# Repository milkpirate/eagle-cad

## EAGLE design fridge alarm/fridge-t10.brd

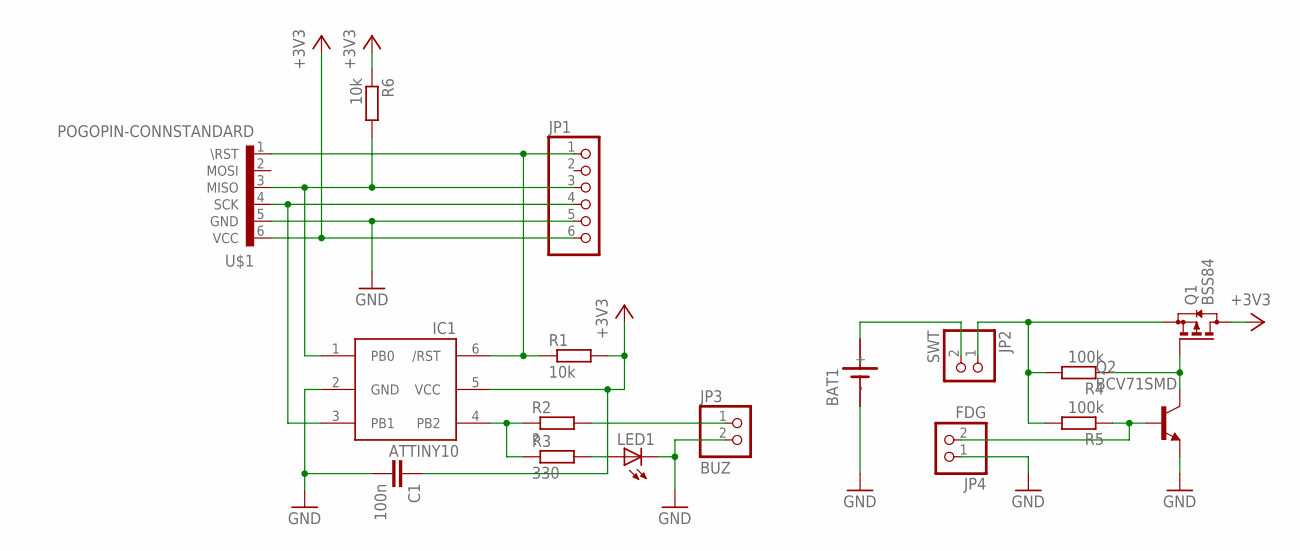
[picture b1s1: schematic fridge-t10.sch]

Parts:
BAT1: SN2032
C1: 100n; C0805K
IC1: ATTINY10; SOT23-6
JP1: PINHD-1X6; 1X06
JP2: SWT; 1X02
JP3: BUZ; 1X02
JP4: FDG; 1X02
LED1: LEDCHIPLED_0805; CHIPLED_0805
Q1: BSS84; SOT23
Q2: BCV71SMD; SOT23-BEC
R1, R6: 10k; R0805
R2: ?; R0805
R3: 330; R0805
R4, R5: 100k; R0805
U$1: POGOPIN-CONNSTANDARD; POGOPROG-CONN

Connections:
+3V3: C1.1, IC1.5 (VCC), JP1.6, Q1.3 (D), R1.2, R6.1, U$1.6 (VCC)
GND: BAT1.-, C1.2, IC1.2 (GND), JP1.5, JP3.2, JP4.1, LED1.C, Q2.E, U$1.5 (GND)
unnamed: BAT1.+, JP2.2
unnamed: IC1.4 (PB2), R2.1, R3.1
unnamed: IC1.1 (PB0), JP1.3, R6.2, U$1.3 (MISO)
unnamed: LED1.A, R3.2
unnamed: IC1.6 (/RST), JP1.1, R1.1, U$1.1 (\RST)
unnamed: JP3.1, R2.2
unnamed: JP2.1, Q1.2 (S), R4.2, R5.2
unnamed: IC1.3 (PB1), JP1.4, U$1.4 (SCK)
unnamed: JP4.2, Q2.B, R5.1
unnamed: Q1.1 (G), Q2.C, R4.1

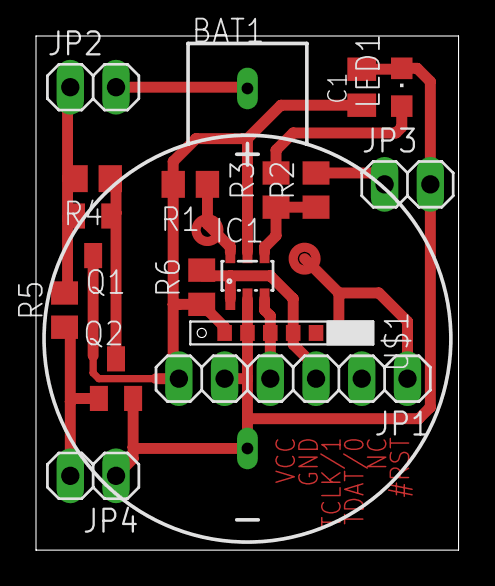
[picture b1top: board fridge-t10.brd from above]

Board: 2 copper layers, 23.5 x 28.6 mm, 17 parts (0 on the bottom side), 12 nets.

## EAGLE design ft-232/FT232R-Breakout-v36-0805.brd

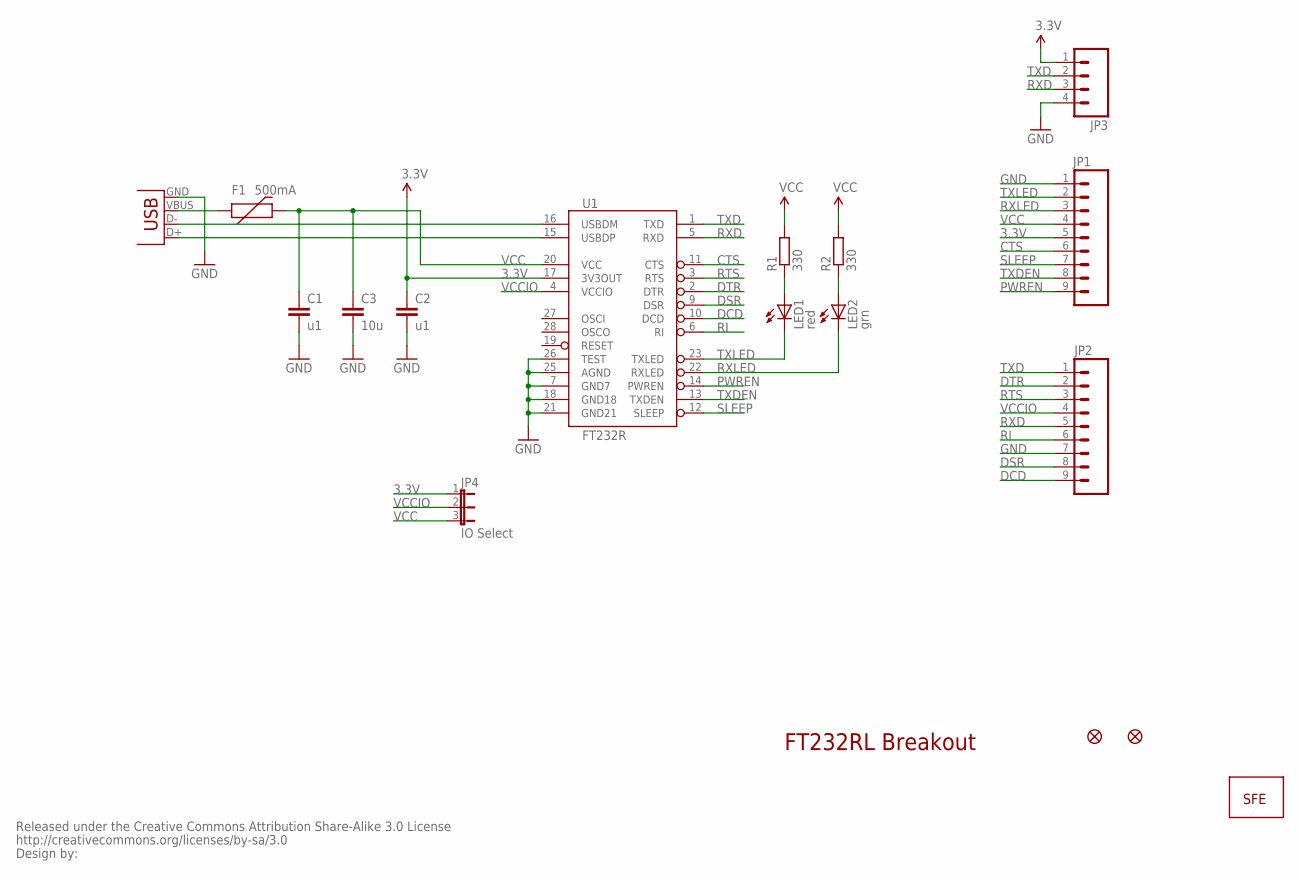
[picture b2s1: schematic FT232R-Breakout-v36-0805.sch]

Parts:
C1, C2: u1; C0805K
C3: 10u; C0805K
F1: 500mA; 0603
JP1, JP2: M09; 1X09
JP3: M04PTH; 1X04
JP4: IO Select; SJ_3
JP5, JP6: FIDUCIAL1X2; FIDUCIAL-1X2
LED1: red; CHIP-LED0805
LED2: grn; CHIP-LED0805
R1, R2: 330; M0805
U1: FT232R; SSOP28DB
U$1: CREATIVE_COMMONS
U$2: LOGO-SFENEW; SFE-NEW-WEBLOGO
X2: USBSMD; USB-MINIB

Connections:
3.3V: C2.1, JP1.5, JP3.1, JP4.1, U1.17 (3V3OUT)
CTS: JP1.6, U1.11 (CTS)
DCD: JP2.9, U1.10 (DCD)
DSR: JP2.8, U1.9 (DSR)
DTR: JP2.2, U1.2 (DTR)
GND: C1.2, C2.2, C3.2, JP1.1, JP2.7, JP3.4, U1.7 (GND7), U1.18 (GND18), U1.21 (GND21), U1.25 (AGND), U1.26 (TEST), X2.GND
unnamed: LED1.A, R1.1
unnamed: LED2.A, R2.1
unnamed: F1.1, X2.VBUS
PWREN: JP1.9, U1.14 (PWREN)
RI: JP2.6, U1.6 (RI)
RTS: JP2.3, U1.3 (RTS)
RXD: JP2.5, JP3.3, U1.5 (RXD)
RXLED: JP1.3, LED2.C, U1.22 (RXLED)
SLEEP: JP1.7, U1.12 (SLEEP)
TXD: JP2.1, JP3.2, U1.1 (TXD)
TXDEN: JP1.8, U1.13 (TXDEN)
TXLED: JP1.2, LED1.C, U1.23 (TXLED)
USB_D+: U1.15 (USBDP), X2.D+
USB_D-: U1.16 (USBDM), X2.D-
VCC: C1.1, C3.1, F1.2, JP1.4, JP4.3, R1.2, R2.2, U1.20 (VCC)
VCCIO: JP2.4, JP4.2, U1.4 (VCCIO)

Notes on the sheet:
FT232RL Breakout

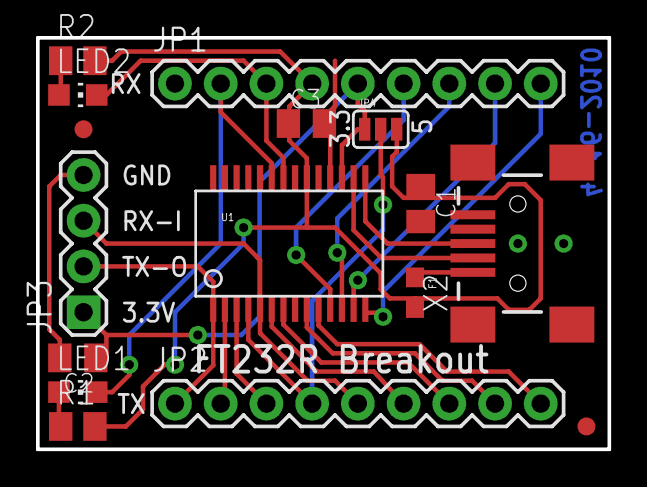
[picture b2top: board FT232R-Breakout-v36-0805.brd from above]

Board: 2 copper layers, 31.8 x 22.9 mm, 18 parts (1 on the bottom side), 22 nets.

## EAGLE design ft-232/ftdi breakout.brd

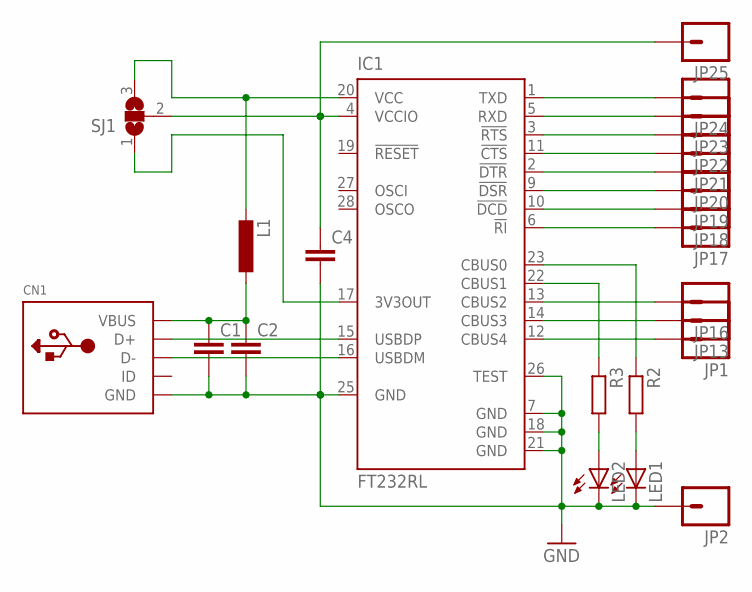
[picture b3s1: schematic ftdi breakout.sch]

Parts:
C1, C2, C4: C-EUC1206K; C1206K
CN1: USBMINIB; USB-MINIB
IC1: FT232RL; SSOP28
JP1, JP2, JP13, JP16, JP17, JP18, JP19, JP20, JP21, JP22, JP23, JP24, JP25: M01PTH_LONGPAD; 1X01_LONGPAD
L1: L-EUL2825P; L2825P
LED1, LED2: LEDCHIPLED_0805; CHIPLED_0805
R2: R-EU_M0805; M0805
R3: R-EU_R0805; R0805
SJ1: SJ2W; SJ_2

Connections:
GND: C1.2, C2.2, C4.2, CN1.GND, IC1.7 (GND), IC1.18 (GND), IC1.21 (GND), IC1.25 (GND), IC1.26 (TEST), JP2.1, LED1.C, LED2.C
unnamed: IC1.23 (CBUS0), R2.1
unnamed: CN1.D+, IC1.15 (USBDP)
unnamed: CN1.D-, IC1.16 (USBDM)
unnamed: C1.1, C2.1, CN1.VBUS, L1.1
unnamed: IC1.20 (VCC), L1.2, SJ1.3
unnamed: C4.1, IC1.4 (VCCIO), JP25.1, SJ1.2
unnamed: IC1.17 (3V3OUT), SJ1.1
unnamed: LED2.A, R3.2
unnamed: LED1.A, R2.2
unnamed: IC1.22 (CBUS1), R3.1
unnamed: IC1.6 (!RI), JP17.1
unnamed: IC1.10 (!DCD), JP18.1
unnamed: IC1.9 (!DSR), JP19.1
unnamed: IC1.2 (!DTR), JP20.1
unnamed: IC1.11 (!CTS), JP21.1
unnamed: IC1.3 (!RTS), JP22.1
unnamed: IC1.5 (RXD), JP23.1
unnamed: IC1.1 (TXD), JP24.1
unnamed: IC1.12 (CBUS4), JP1.1
unnamed: IC1.13 (CBUS2), JP16.1
unnamed: IC1.14 (CBUS3), JP13.1

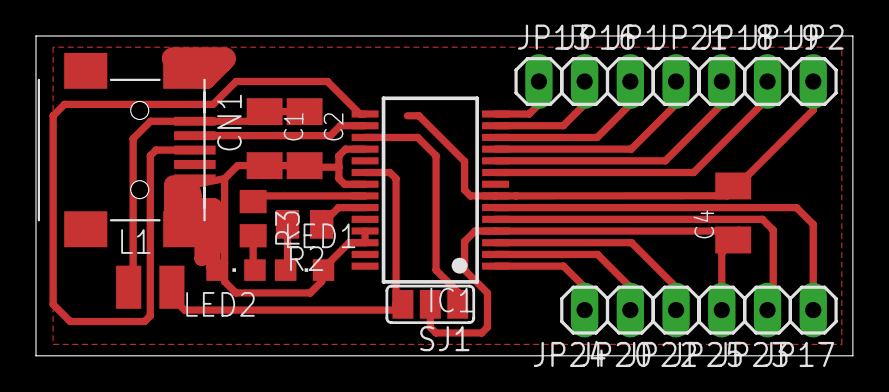
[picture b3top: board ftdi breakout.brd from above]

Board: 2 copper layers, 45.4 x 17.8 mm, 24 parts (0 on the bottom side), 22 nets.

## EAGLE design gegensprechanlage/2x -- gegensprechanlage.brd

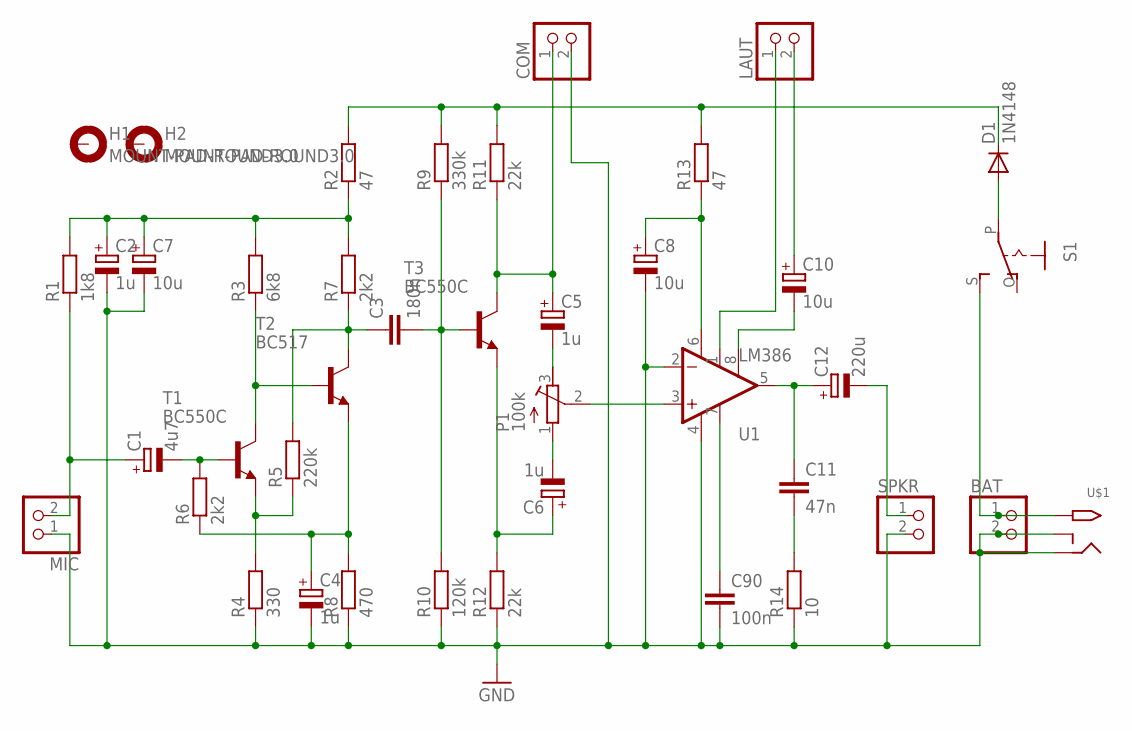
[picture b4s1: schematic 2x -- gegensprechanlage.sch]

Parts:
BAT: PINHD-1X2; 1X02
C1: 4u7; E2,5-6
C2, C4, C5, C6: 1u; E2,5-6
C3: 180n; C025-025X050
C7, C8, C10: 10u; E2,5-6
C11: 47n; C025-025X050
C12: 220u; E2,5-6
C90: 100n; C025-025X050
COM: PINHD-1X2; 1X02
D1: 1N4148; D-7.5
H1, H2: MOUNT-PAD-ROUND3.0; 3,0-PAD
LAUT: PINHD-1X2; 1X02
MIC: PINHD-1X2; 1X02
P1: 100k; RTRIM64P
R1: 1k8; 0204/7
R2, R13: 47; 0204/7
R3: 6k8; 0204/7
R4: 330; 0204/7
R5: 220k; 0204/7
R6, R7: 2k2; 0204/7
R8: 470; 0204/7
R9: 330k; 0204/7
R10: 120k; 0204/7
R11, R12: 22k; 0204/7
R14: 10; 0204/7
S1: EG1218S; EG1218
SPKR: PINHD-1X2; 1X02
T1, T3: BC550C; TO92-CBE
T2: BC517; TO92-CBE
U1: LM386; DIP08
U$1: 2.1MMJACKTHM; PJ-102A

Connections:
GND: BAT.2, C2.-, C4.-, C7.-, C8.-, C90.2, COM.2, MIC.1, R4.1, R8.1, R10.1, R12.1, R14.1, SPKR.2, U1.2 (-IN), U1.4 (V-), U$1.RING, U$1.RING_SW
unnamed: C1.-, R6.2, T1.B
unnamed: C1.+, MIC.2, R1.1
unnamed: R3.1, T1.C, T2.B
unnamed: R4.2, R5.1, T1.E
unnamed: C3.1, R5.2, R7.1, T2.C
unnamed: C10.+, LAUT.2
unnamed: C4.+, R6.1, R8.2, T2.E
unnamed: C2.+, C7.+, R1.2, R2.1, R3.2, R7.2
unnamed: C3.2, R9.1, R10.2, T3.B
unnamed: D1.C, R2.2, R9.2, R11.2, R13.2
unnamed: C10.-, U1.8 (GAIN)
unnamed: C6.+, R12.2, T3.E
unnamed: C6.-, P1.1 (A)
unnamed: P1.2 (S), U1.3 (+IN)
unnamed: C5.+, COM.1, R11.1, T3.C
unnamed: C5.-, P1.3 (E)
unnamed: C90.1, U1.7 (BP)
unnamed: C8.+, R13.1, U1.6 (V+)
unnamed: LAUT.1, U1.1 (GAIN)
unnamed: C11.1, C12.+, U1.5 (OUT)
unnamed: C11.2, R14.2
unnamed: C12.-, SPKR.1
unnamed: BAT.1, S1.S, U$1.TIP
unnamed: D1.A, S1.P

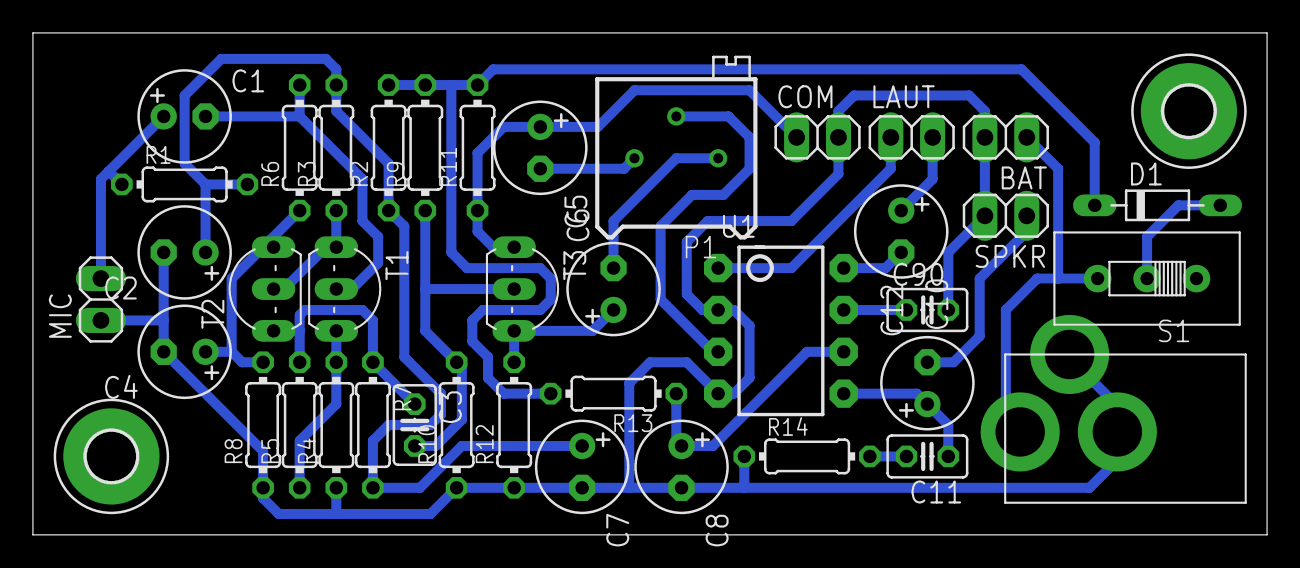
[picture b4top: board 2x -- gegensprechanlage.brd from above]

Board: 2 copper layers, 74.9 x 30.5 mm, 41 parts (0 on the bottom side), 25 nets.

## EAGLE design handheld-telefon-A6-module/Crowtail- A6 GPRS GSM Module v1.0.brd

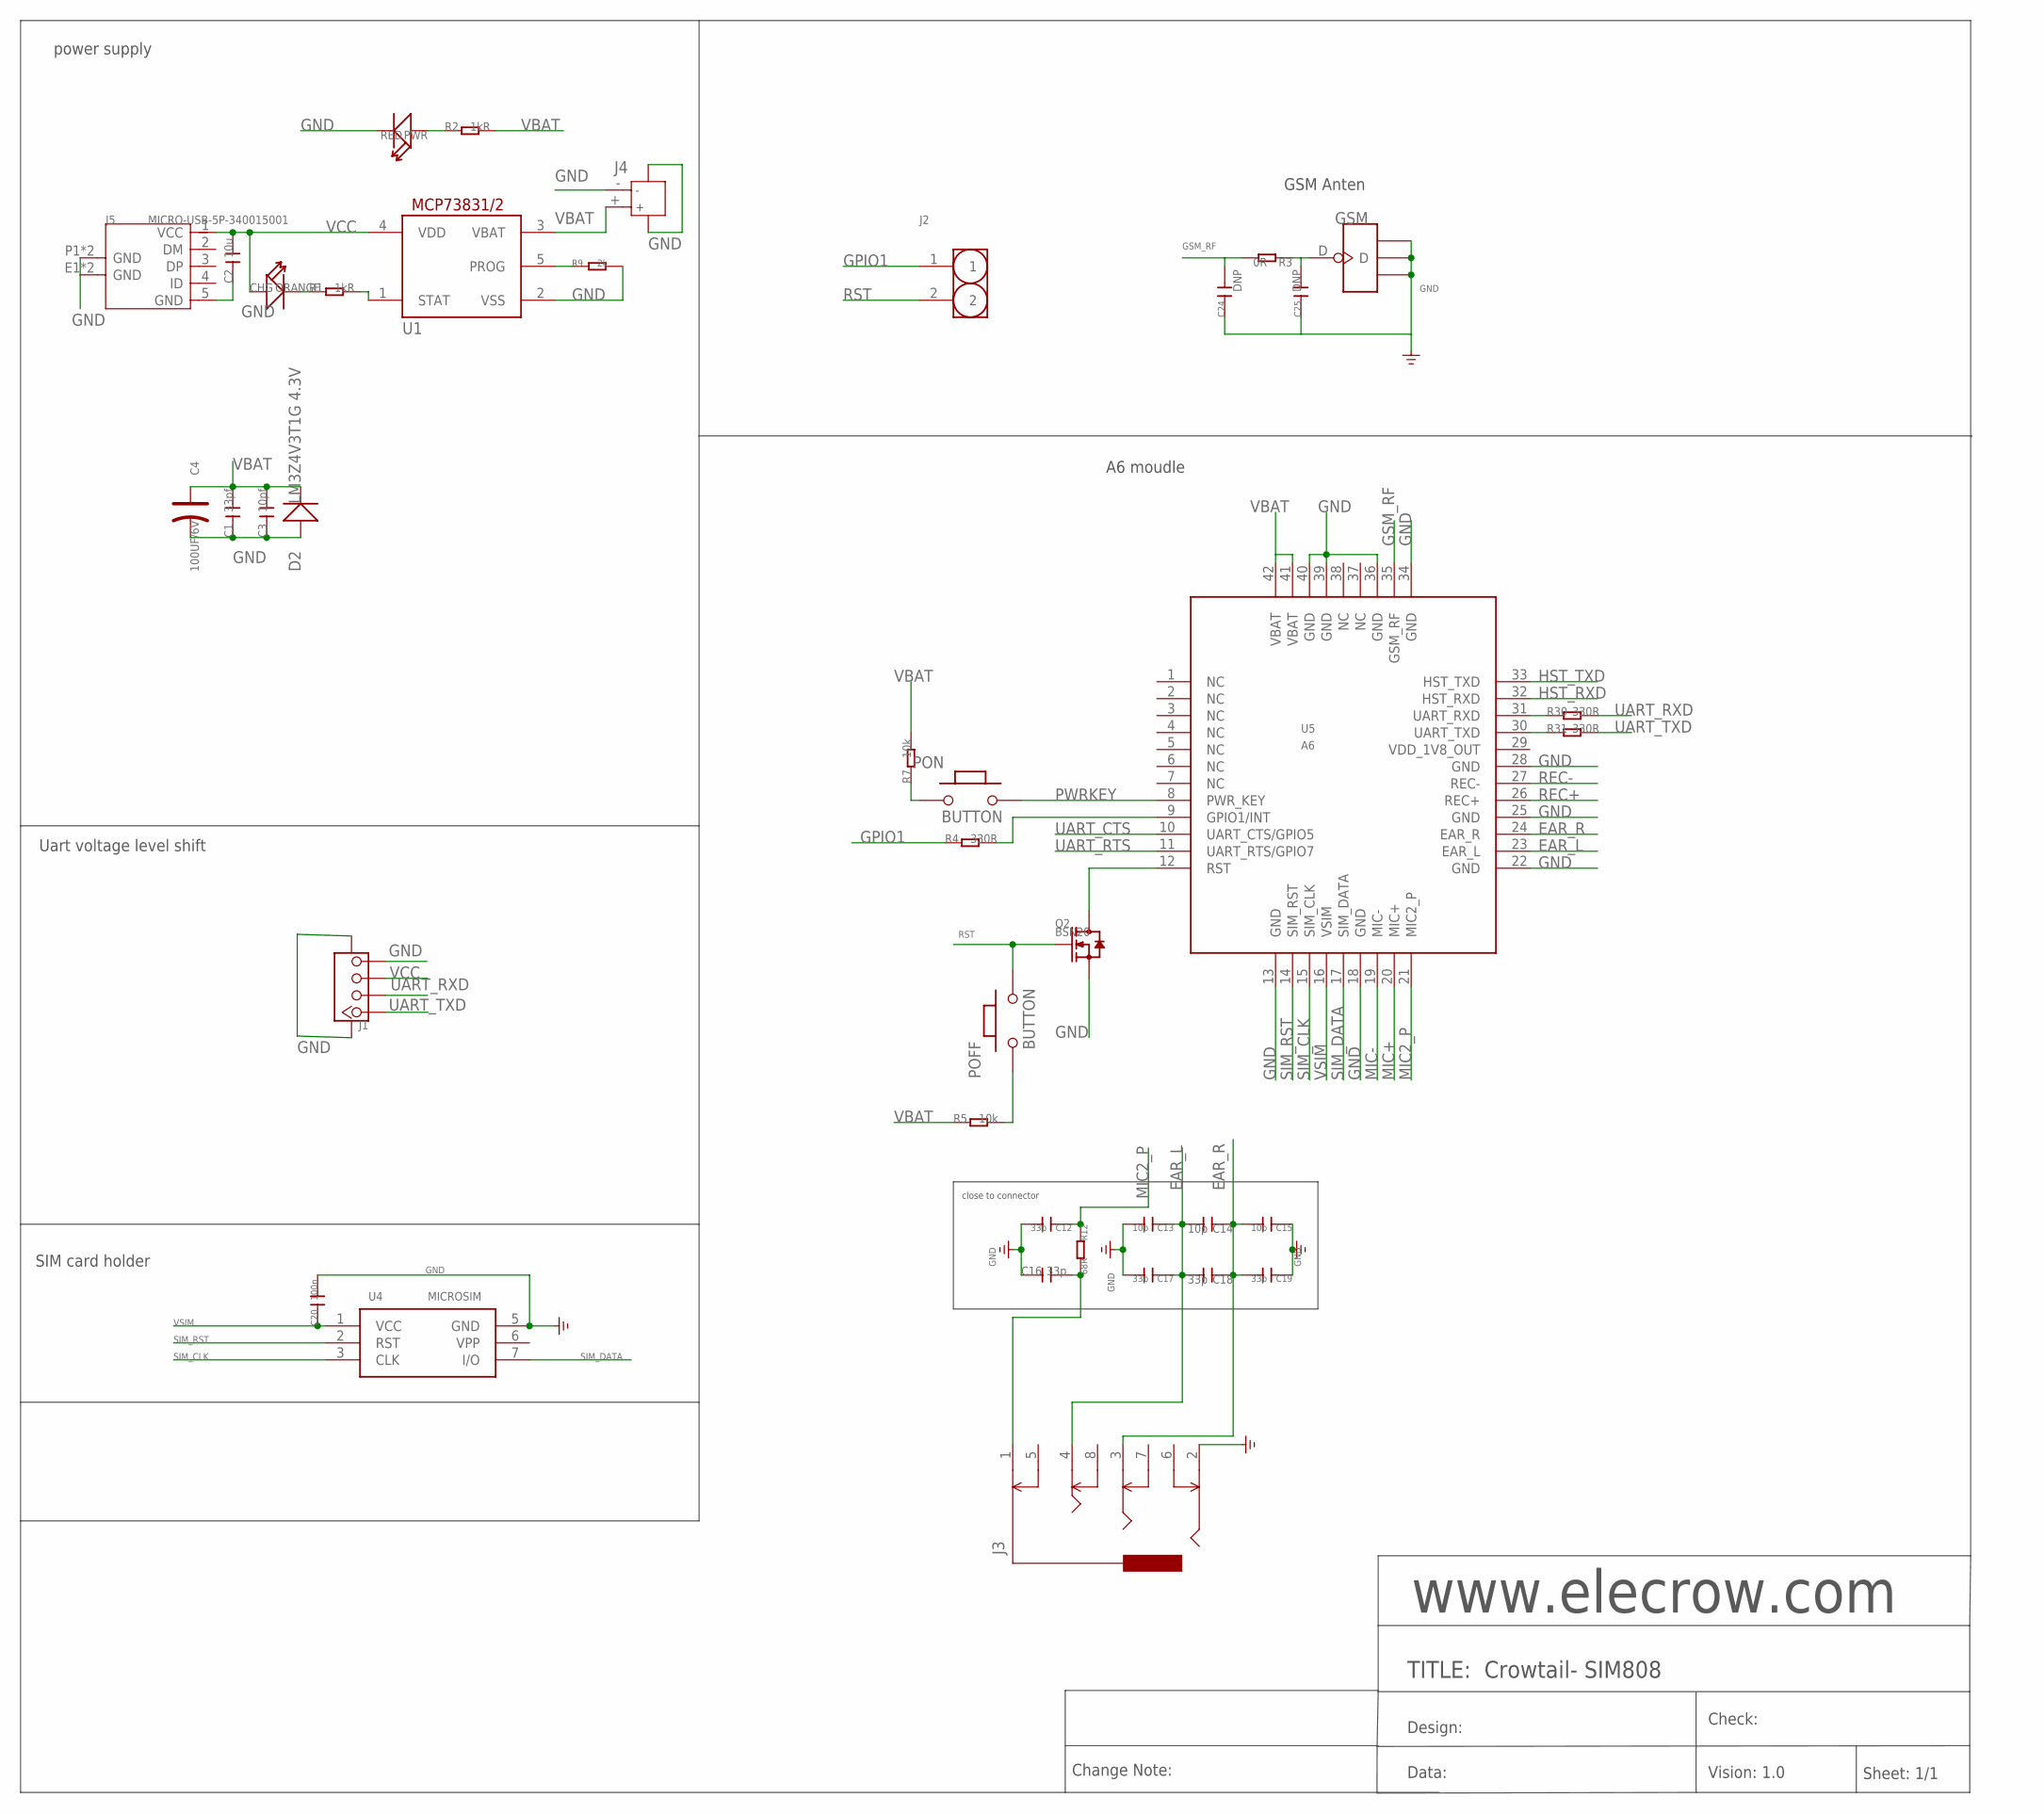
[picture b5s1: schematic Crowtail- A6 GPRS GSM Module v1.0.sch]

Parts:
C1: 33pf; C0603
C2: 10u; C0603
C3: 10pf; C0603
C4: 100UF/6V; AVX-A
C12, C16: 33p; C0603
C13, C14, C15: 10p; C0402
C17, C18, C19: 33p; C0402
C20: 100n; C0603
C24, C25: DNP; C0402
CHG: ORANGE; D0603
D2: LM3Z4V3T1G 4.3V; SOD323
GSM: ANTENNA-U-FL; 4P-U-FL
J1: TWIG-4P-2.0-SMD-FEMALE-REINFORCE'90D'; 4P-SMD-2.0-90D
J2: HEADER-2P-65/35MIL; 2P-2.54-65/35MIL
J3: AUDIO-8P'PJ-3536-L6S'; 8P-3.5-SMD
J4: JACK-JST-2P-SMD-PW'2.0'; JST-SMD-2.0-90D
J5: MICRO-USB-5P-340015001; B-SMD-5P
POFF: BUTTON; 157SW
PON: BUTTON; 157SW
PWR: RED; D0603
Q2: BSN20; SOT23
R1, R2: 1kR; R0603
R3: 0R; R0603
R4, R30, R31: 330R; R0603
R5, R7: 10k; R0603
R9: 2k; R0603
R12: 68R; R0603
U1: MCP73831/OT; SOT23-5L
U4: MICROSIM
U5: A6

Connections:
EAR_L: C13.1, C14.2, C17.1, C18.2, J3.4, U5.23 (EAR_L)
EAR_R: C14.1, C15.2, C18.1, C19.2, J3.3, U5.24 (EAR_R)
GND: C1.1, C2.1, C3.1, C4.-, C12.2, C13.2, C15.1, C16.1, C17.2, C19.1, C20.2, C24.1, C25.1, D2.+, GSM.GND1, GSM.GND2, GSM.GND3, J1.4, J1.SS1, J1.SS2, J3.2, J4.3, J4.4, J4.- (2), J5.5 (GND), J5.E1 (GND), J5.E2 (GND), J5.P1 (GND), J5.P2 (GND), PWR.-, Q2.2 (S), R9.2, U1.2 (VSS), U4.5 (GND), U5.13 (GND), U5.18 (GND), U5.22 (GND), U5.25 (GND), U5.28 (GND), U5.34 (GND), U5.36 (GND), U5.39 (GND), U5.40 (GND)
GPIO1: J2.1, R4.1
GSM_RF: C24.2, R3.2, U5.35 (GSM_RF)
HST_RXD: U5.32 (HST_RXD)
HST_TXD: U5.33 (HST_TXD)
MIC2_P: C12.1, R12.1, U5.21 (MIC2_P)
MIC+: U5.20 (MIC+)
MIC-: U5.19 (MIC-)
unnamed: POFF.1, R5.2
unnamed: C25.2, GSM.D, R3.1
unnamed: PWR.+, R2.1
unnamed: R30.1, U5.31 (UART_RXD)
unnamed: R31.1, U5.30 (UART_TXD)
unnamed: PON.1, R7.1
unnamed: CHG.-, R1.1
unnamed: Q2.3 (D), U5.12 (RST)
unnamed: R4.2, U5.9 (GPIO1/INT)
unnamed: R1.2, U1.1 (STAT)
unnamed: C16.2, J3.1, R12.2
unnamed: R9.1, U1.5 (PROG)
PWRKEY: PON.2, U5.8 (PWR_KEY)
REC+: U5.26 (REC+)
REC-: U5.27 (REC-)
RST: J2.2, POFF.2, Q2.1 (G)
SIM_CLK: U4.3 (CLK), U5.15 (SIM_CLK)
SIM_DATA: U4.7 (I/O), U5.17 (SIM_DATA)
SIM_RST: U4.2 (RST), U5.14 (SIM_RST)
UART_CTS: U5.10 (UART_CTS/GPIO5)
UART_RTS: U5.11 (UART_RTS/GPIO7)
UART_RXD: J1.2, R30.2
UART_TXD: J1.1, R31.2
VBAT: C1.2, C3.2, C4.+, D2.-, J4.+ (1), R2.2, R5.1, R7.2, U1.3 (VBAT), U5.41 (VBAT), U5.42 (VBAT)
VCC: C2.2, CHG.+, J1.3, J5.1 (VCC), U1.4 (VDD)
VSIM: C20.1, U4.1 (VCC), U5.16 (VSIM)

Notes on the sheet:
TITLE: Crowtail- SIM808
www.elecrow.com
Design:
Check:
Data:
Vision: 1.0
Sheet: 1/1
power supply
Uart voltage level shift
SIM card holder
Change Note:
GSM Anten
A6 moudle
close to connector

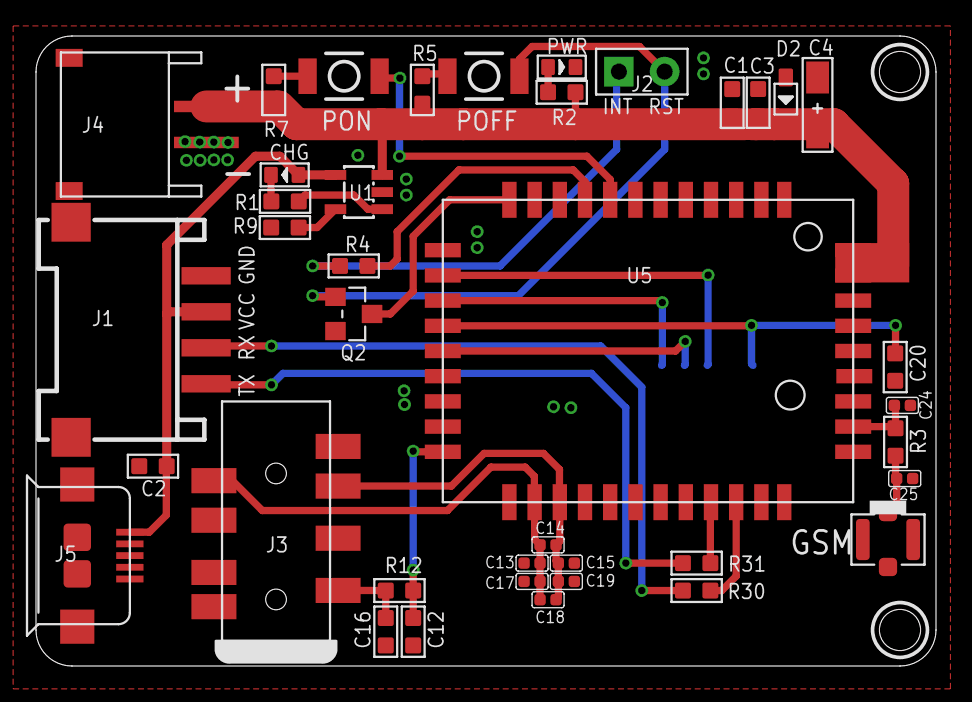
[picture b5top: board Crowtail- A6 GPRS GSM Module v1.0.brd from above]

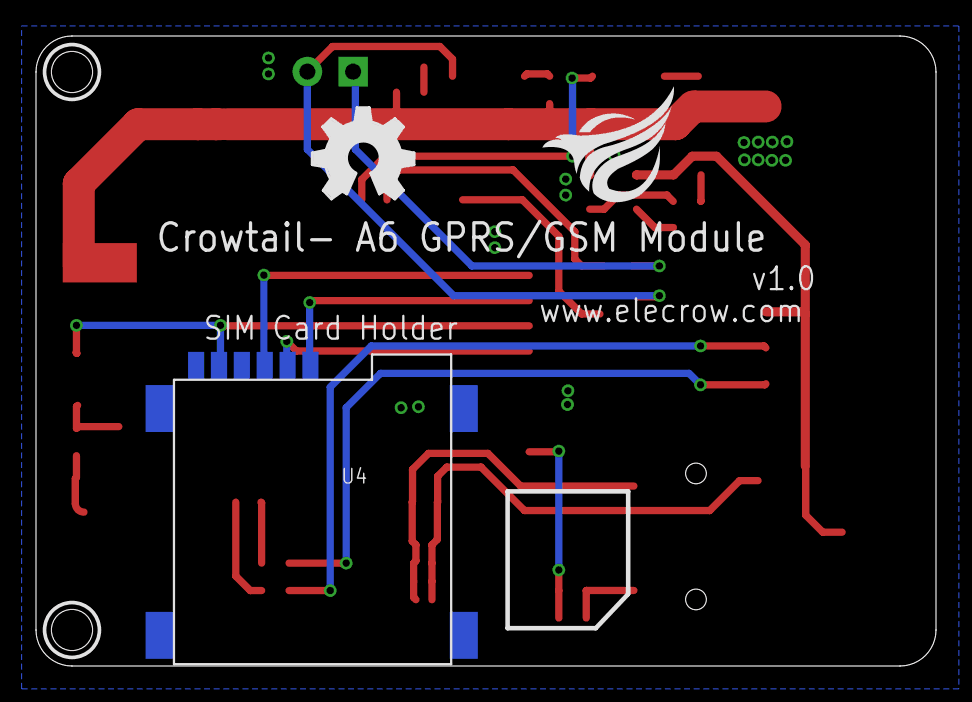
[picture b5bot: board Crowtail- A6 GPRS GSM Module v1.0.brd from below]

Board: 2 copper layers, 50.0 x 35.0 mm, 42 parts (3 on the bottom side), 28 nets.

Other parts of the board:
LOGO2: LOGO-OSHW-FILLX0200-NT; OSHW_FILLX200_NOTEXT
U$4: ELECROW_NRW_6

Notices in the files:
parts and their libraries:
SparkFun: Released under the Creative Commons Attribution Share-Alike 3.0 License
SparkFun: http://creativecommons.org/licenses/by-sa/3.0
SparkFun-AnalogIC: Licensing:Creative Commons ShareAlike 4.0 International - https://creativecommons.org/licenses/by-sa/4.0
